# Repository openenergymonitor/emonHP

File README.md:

# emonHP - Heat Pump Monitoring

**As of Aug 2026 emonHP2 hardware is not yet released**

## Introduction

_emonHP V2_ is a system for monitoring heat pump operation. It is designed to work with [OpenEnergyMonitor](https://openenergymonitor.org), but can be used as a standalone system.

The system provides the following interfaces:

- MBUS
- RS485
- DHW, pulse, and OneWire (DS218B20 temperature) inputs
- USB-C power 
- 40-pin Raspberry Pi header
- OLED I2C display
- RFM69CW RF transceiver 

The board uses a STM32C031K6U microcontroller

## Getting started

### Getting a board

- Purchase a heat pump monitoring system from the [OpenEnergyMonitor Shop](https://shop.openenergymonitor.com/)
- Build your own!
  - With [KiCad](https://www.kicad.org/) installed, run `./generate.py` in the `pcb` directory (tested on Linux and macOS only) to generate manufacturing files (KiCad PCB, Gerbers, BoM).

### emonHP2

> [!NOTE]
Setting up as an integrated emonHP system requires a Raspberry Pi 4 or 5. These expose extra UART ports on the 40-pin header which are not available on older versions.

Connect the Raspberry Pi to the 40 pin header.

> [!WARNING]
Power must only be applied to one of the emonHP's USB-C port *or* the Raspberry Pi's power port, never both.

### Connections 

- DHW Status: Signal 1 input - GPIO27 - Pin 13 
- Pulse: Signal 2 input - GPIO22 - Pin15 - soft-pull down enabled (NOT TESTED)
- OneWire (DS18B20 ) - Signal 3 input - GPIO0*

\* Set `dtoverlay=w1-gpio,gpiopin=0` in `/boot/firmware/config.txt` to support OneWire on GPIO0

 - Push button - GPIO17 - pin11: set `push_btn = Button(17, pull_up=True, bounce_time=0.1, hold_time=5)` in `emonPiLCD2.py` 

### Firmware & Rasi Setup 

See firmware repo: https://github.com/openenergymonitor/emonhp-rs

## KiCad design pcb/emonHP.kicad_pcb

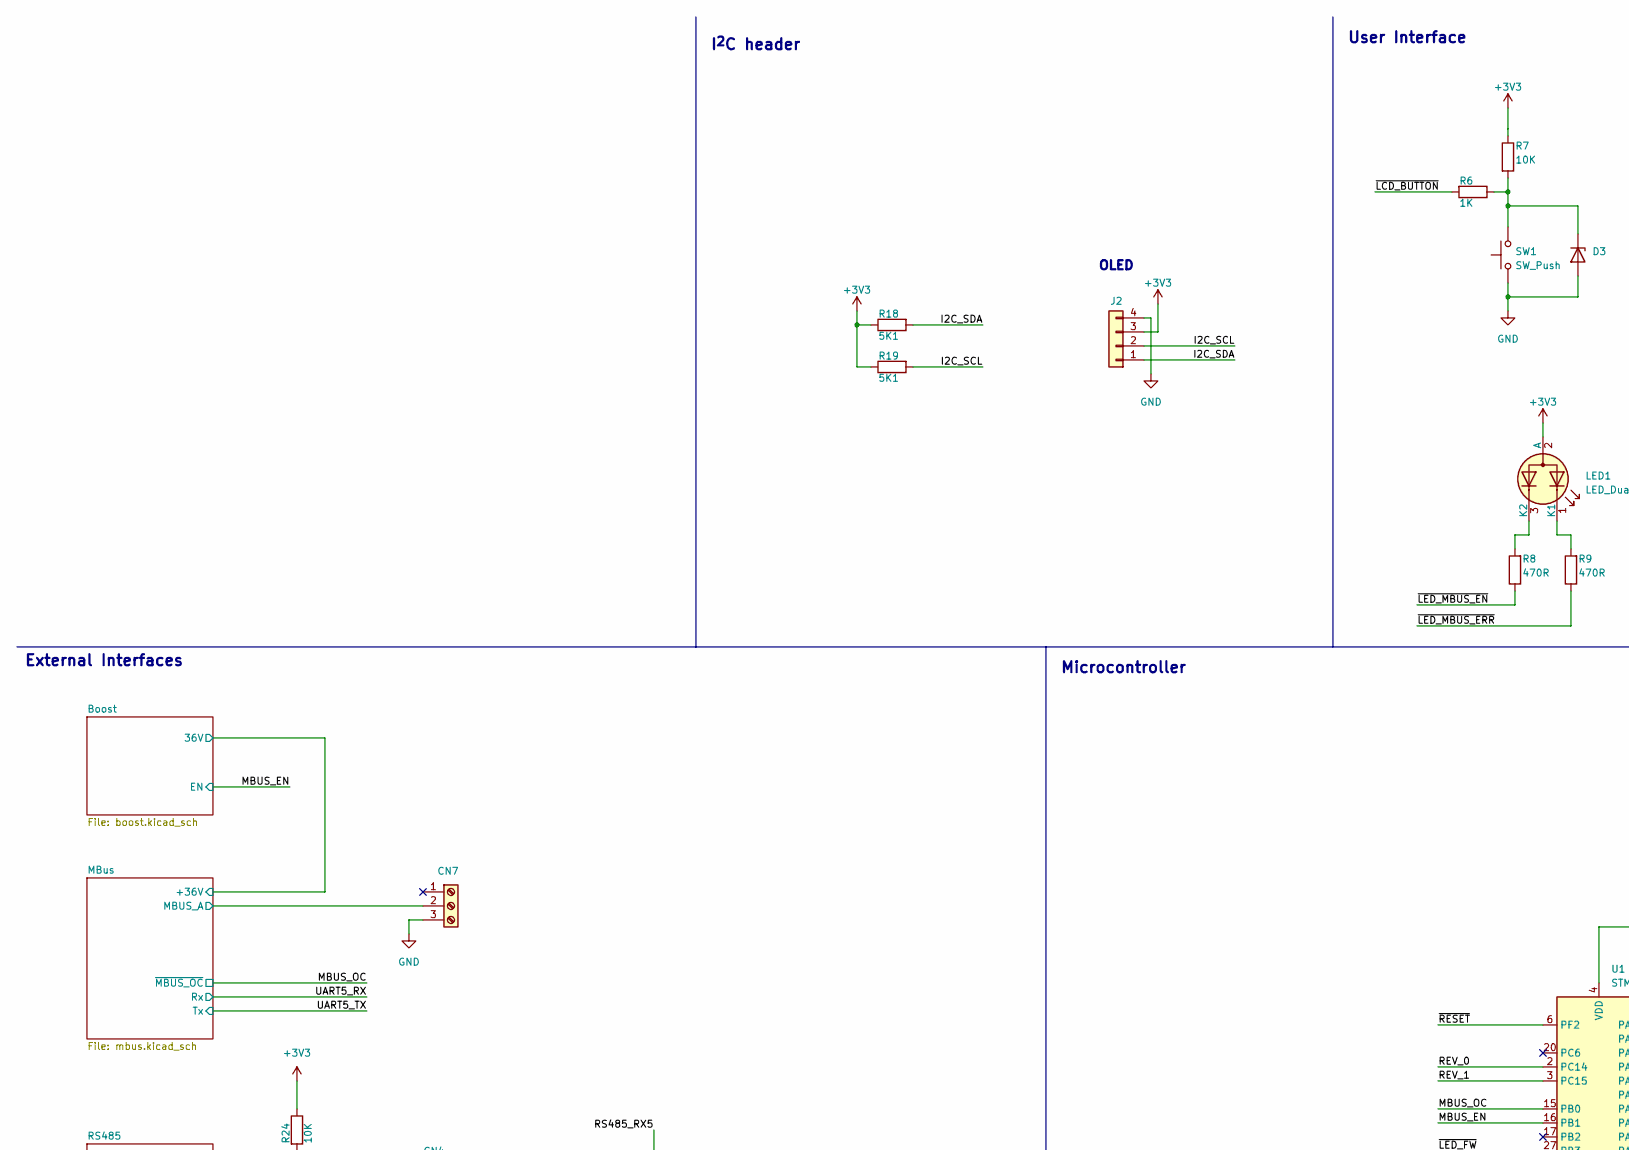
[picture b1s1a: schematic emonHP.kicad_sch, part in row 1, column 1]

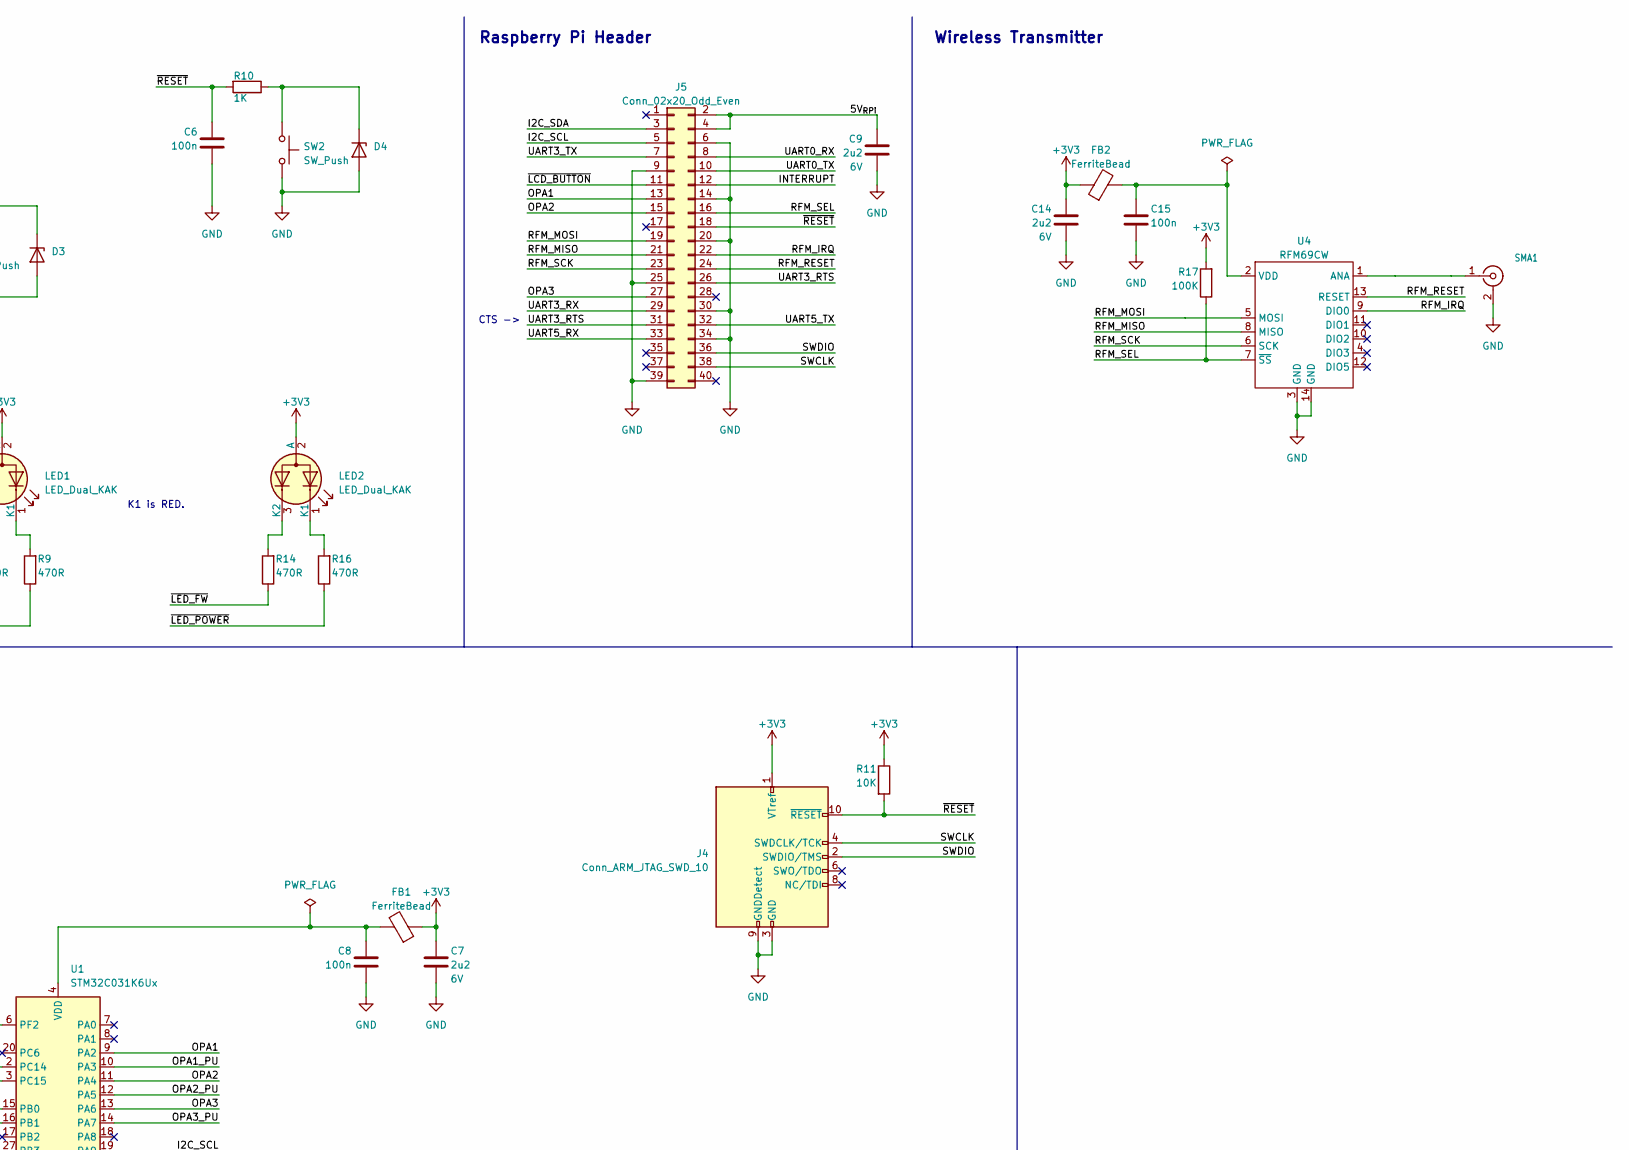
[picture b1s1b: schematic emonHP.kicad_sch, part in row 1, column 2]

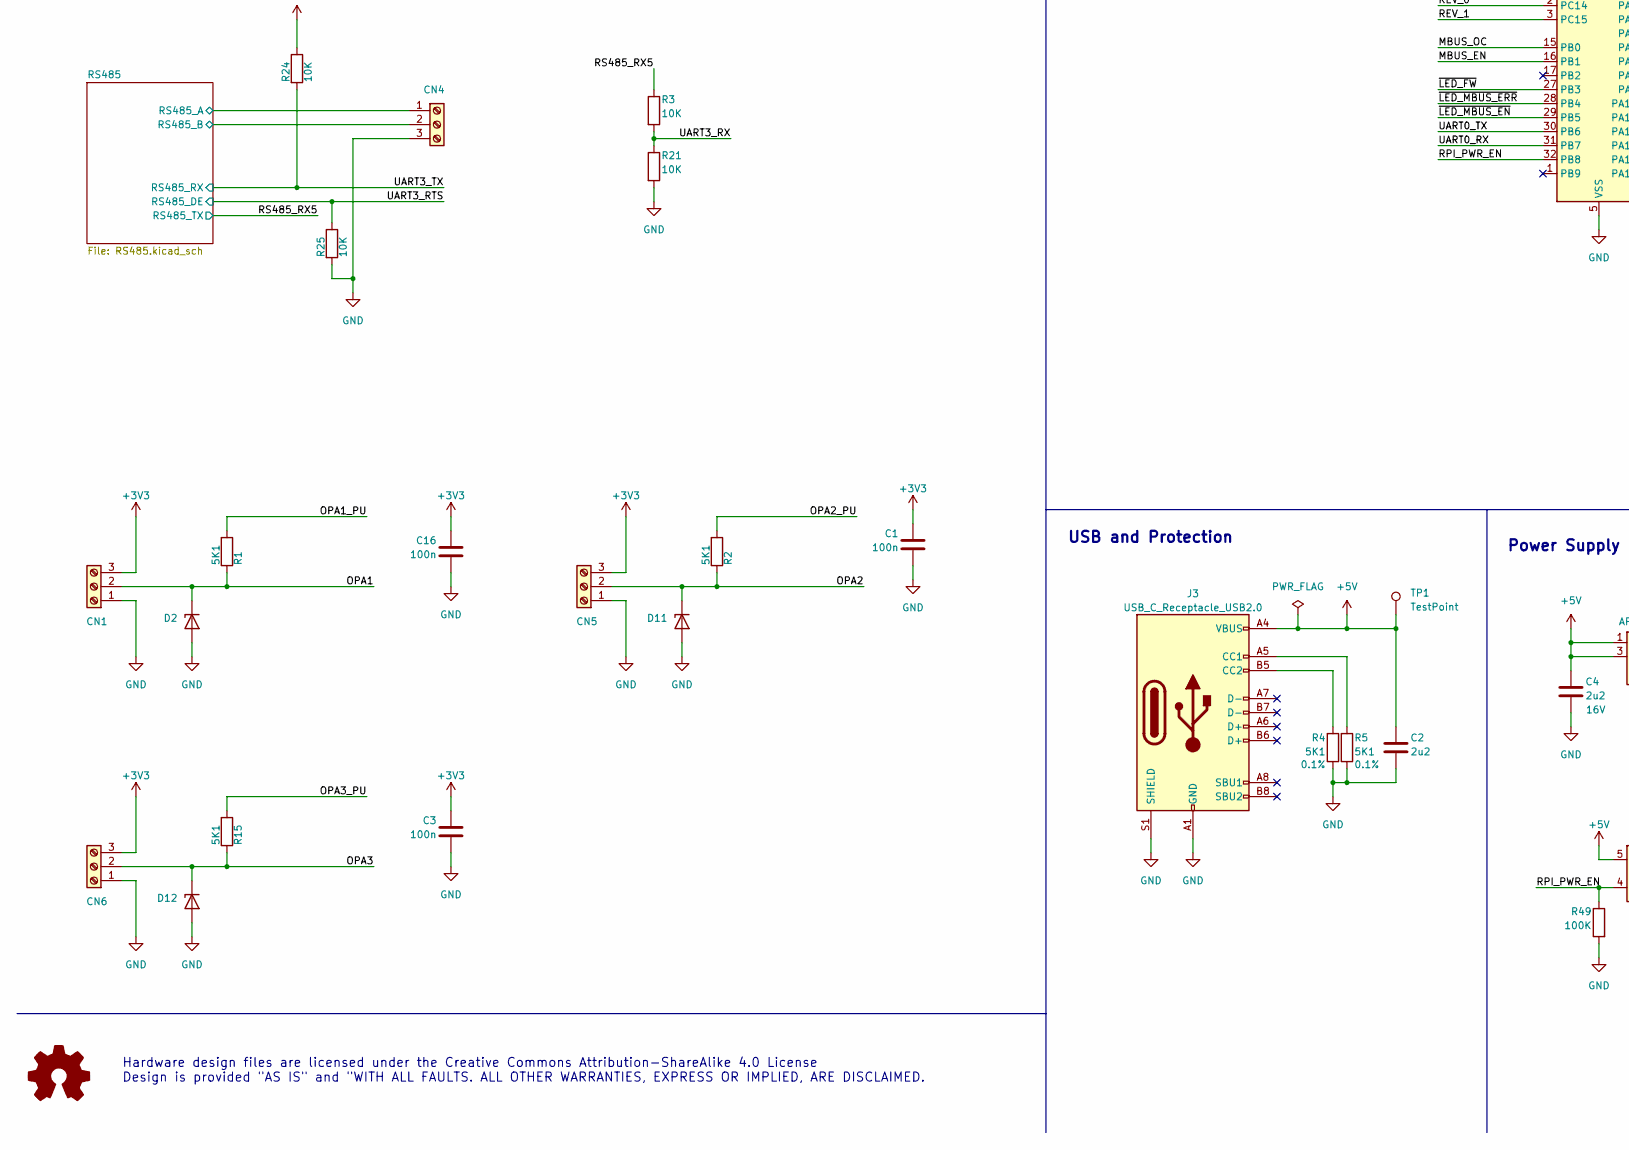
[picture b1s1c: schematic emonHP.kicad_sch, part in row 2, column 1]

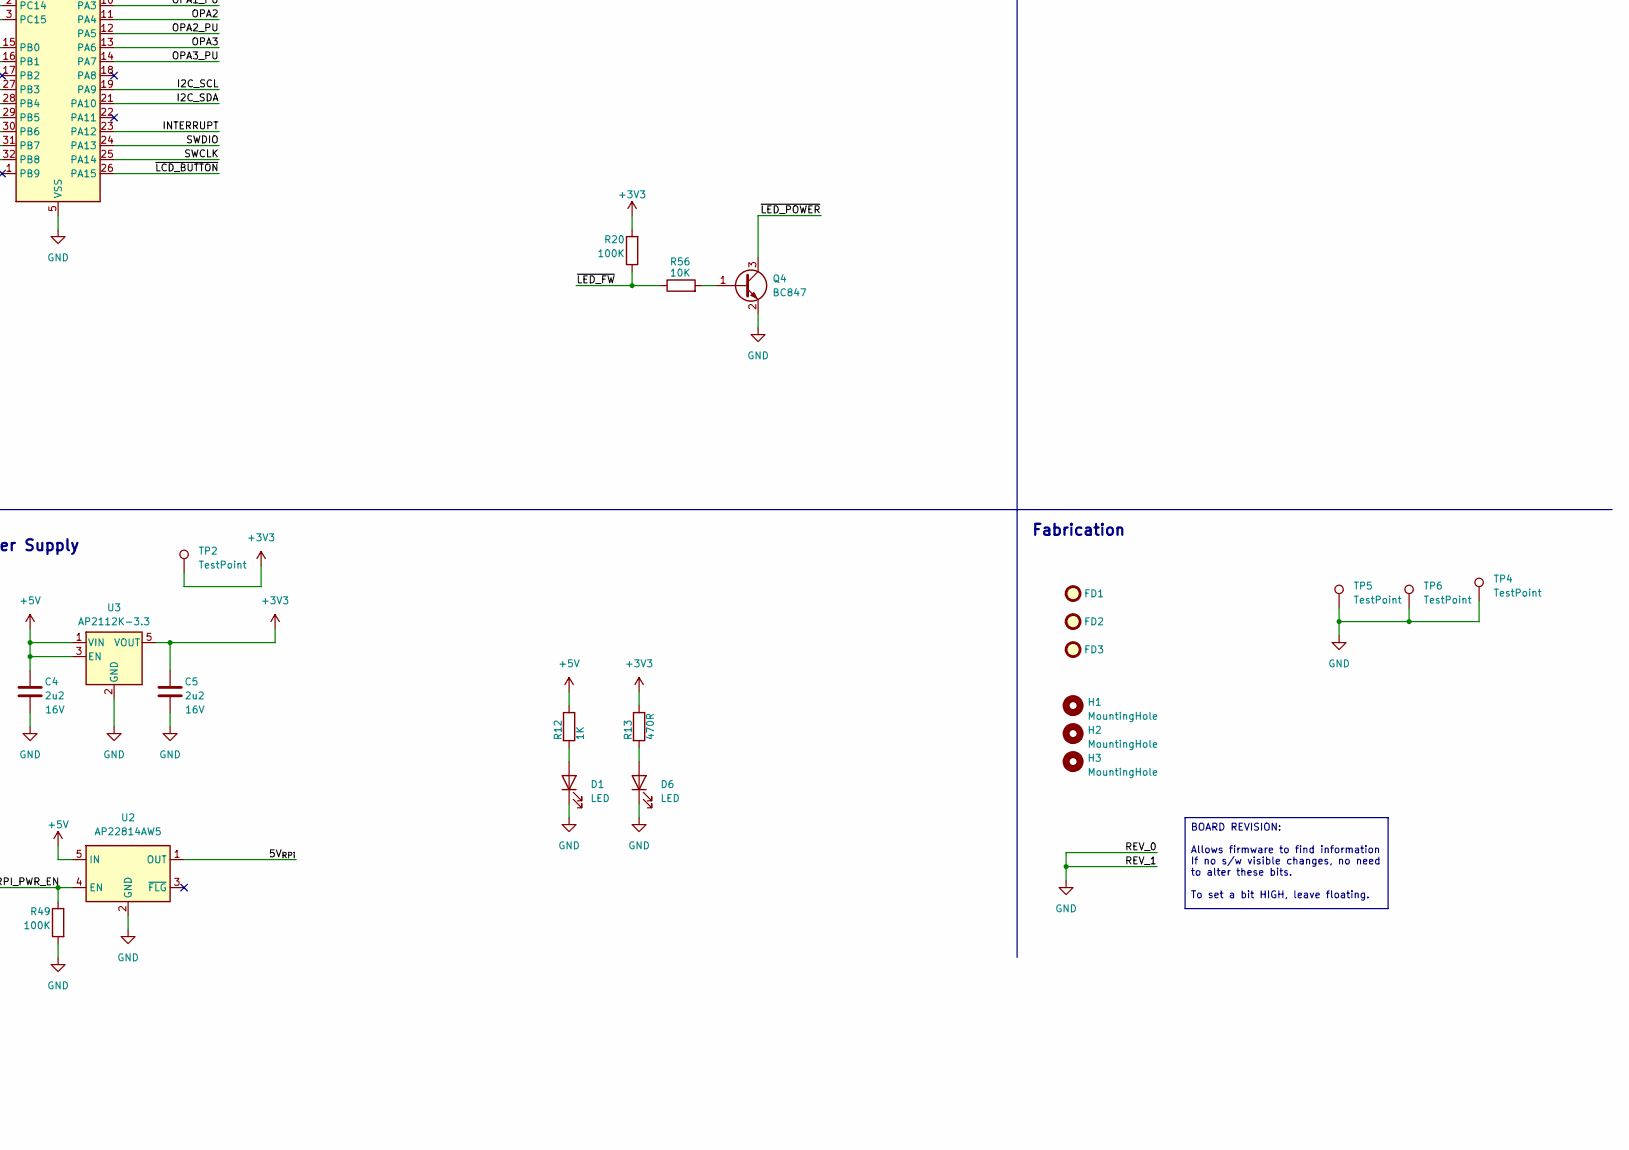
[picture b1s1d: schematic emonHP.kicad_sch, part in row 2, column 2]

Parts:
C1, C3, C6, C8, C15, C16: 100n; C_0402_1005Metric; LCSC C1525
C2: 2u2; C_0402_1005Metric; LCSC C12530
C4, C5: 2u2; C_0603_1608Metric; Voltage 16V; LCSC C23630
C7, C9, C14: 2u2; C_0402_1005Metric; Voltage 6V; LCSC C12530
CN1, CN4, CN5, CN6, CN7: CONN_03SCREW; TerminalBlock_Phoenix_PT-1,5-3-3.5-H_1x03_P3.50mm_Horizontal; MPN 5441359; Mouser 651-5441359
D1, D6: LED; LED_0603_1608Metric; LCSC C2286
D2, D3, D4, D11, D12: ESD5Z3.3T5G; D_SOD-523; LCSC C22440024
FB1, FB2: FerriteBead; R_0402_1005Metric; LCSC C237347
FD1, FD2, FD3: FIDUCIAL1X2; Fiducial_0.75mm_Mask1.5mm
H1, H2: MountingHole; MountingHole_2.7mm_M2.5
H3: MountingHole; MountingHole_2.1mm
J2: CONN_04PTH; PinSocket_1x04_P2.54mm_Vertical
J3: USB_C_Receptacle_USB2.0; CSP-USC16-TR; LCSC C2765186
J4: Conn_ARM_JTAG_SWD_10; PinHeader_2x05_P1.27mm_Vertical_SMD; LCSC C150517
J5: Conn_02x20_Odd_Even; REF-182665; LCSC C9900171940
LED1, LED2: LED_Dual_KAK; LTST-S326; MPN LTST-S326KGJRKT; Mouser 859-LTST-S326KGJRKT
Q4: BC847; SOT-23; LCSC C2138
R1, R2, R15, R18, R19: 5K1; R_0402_1005Metric; LCSC C25905
R3, R7, R11, R21, R24, R25, R56: 10K; R_0402_1005Metric; LCSC C25744
R4, R5: 5K1; R_0402_1005Metric; Tolerance 0.1%; MPN ERA-3AED512V; Mouser 667-ERA-3AED512V
R6, R10, R12: 1K; R_0402_1005Metric; LCSC C11702
R8, R9, R13, R14, R16: 470R; R_0402_1005Metric; LCSC C25117
R17, R20, R49: 100K; R_0402_1005Metric; LCSC C25741
SMA1: SMACONNECTOR; SMA_Amphenol_132203-12_Horizontal
SW1: SW_Push; SW_PUSH_6mm
SW2: SW_Push; SW_Tactile_SPST_NO_Straight_CK_PTS636Sx25SMTRLFS; LCSC C2689642
TP1, TP2, TP4, TP5, TP6: TestPoint; TestPoint_Pad_D1.0mm
U1: STM32C031K6Ux; QFN-32-1EP_5x5mm_P0.5mm_EP3.45x3.45mm; LCSC C5456204
U2: AP22814AW5; SOT-23-5; LCSC C2680321
U3: AP2112K-3.3; SOT-23-5; LCSC C51118
U4: RFM69CW

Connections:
+3V3: C1.1, C3.1, C5.2, C7.1, C14.1, C16.1, CN1.3, CN5.3, CN6.3, FB1.1, FB2.1, J2.3, J4.1 (VTref), LED1.2 (A), LED2.2 (A), R7.1, R11.1, R13.1, R17.2, R18.1, R19.1, R20.2, R24.1, TP2.1, U3.5 (VOUT); also elsewhere on the board
+5V: C2.2, C4.2, J3.A4 (VBUS), J3.A9 (VBUS), J3.B4 (VBUS), J3.B9 (VBUS), R12.1, TP1.1, U2.5 (IN), U3.1 (VIN), U3.3 (EN); also elsewhere on the board
/5V_{RPi}: C9.1, J5.2, J5.4, U2.1 (OUT)
/I2C_SCL: J2.2, J5.5, R19.2, U1.19 (PA9)
/I2C_SDA: J2.1, J5.3, R18.2, U1.21 (PA10)
/INTERRUPT: J5.12, U1.23 (PA12)
/MBUS_EN: U1.16 (PB1); also elsewhere on the board
/MBUS_OC: U1.15 (PB0); also elsewhere on the board
/MBus/MBUS_A: CN7.2; also elsewhere on the board
/OPA1: CN1.2, D2.1 (K), J5.13, R1.1, U1.9 (PA2)
/OPA1_PU: R1.2, U1.10 (PA3)
/OPA2: CN5.2, D11.1 (K), J5.15, R2.1, U1.11 (PA4)
/OPA2_PU: R2.2, U1.12 (PA5)
/OPA3: CN6.2, D12.1 (K), J5.27, R15.1, U1.13 (PA6)
/OPA3_PU: R15.2, U1.14 (PA7)
/RFM_IRQ: J5.22, U4.9 (DIO0)
/RFM_MISO: J5.21, U4.8 (MISO)
/RFM_MOSI: J5.19, U4.5 (MOSI)
/RFM_RESET: J5.24, U4.13 (RESET)
/RFM_SCK: J5.23, U4.6 (SCK)
/RFM_SEL: J5.16, R17.1, U4.7 (~SS)
/RPI_PWR_EN: R49.1, U1.32 (PB8), U2.4 (EN)
/RS485/RS485_A: CN4.1; also elsewhere on the board
/RS485/RS485_B: CN4.2; also elsewhere on the board
/RS485_RX5: R3.1; also elsewhere on the board
/SWCLK: J4.4 (SWDCLK/TCK), J5.38, U1.25 (PA14)
/SWDIO: J4.2 (SWDIO/TMS), J5.36, U1.24 (PA13)
/UART0_RX: J5.8, U1.31 (PB7)
/UART0_TX: J5.10, U1.30 (PB6)
/UART3_RTS: J5.26, J5.31, R25.1; also elsewhere on the board
/UART3_RX: J5.29, R3.2, R21.1
/UART3_TX: J5.7, R24.2; also elsewhere on the board
/UART5_RX: J5.33; also elsewhere on the board
/UART5_TX: J5.32; also elsewhere on the board
/~LCD_BUTTON: J5.11, R6.2, U1.26 (PA15)
/~LED_FW: R14.1, R20.1, R56.1, U1.27 (PB3)
/~LED_MBUS_EN: R8.1, U1.29 (PB5)
/~LED_MBUS_ERR: R9.1, U1.28 (PB4)
/~LED_POWER: Q4.3 (C), R16.1
/~RESET: C6.1, J4.10 (~RESET), J5.18, R10.2, R11.2, U1.6 (PF2)
GND: C1.2, C2.1, C3.2, C4.1, C5.1, C6.2, C7.2, C8.2, C9.2, C14.2, C15.2, C16.2, CN1.1, CN4.3, CN5.1, CN6.1, CN7.3, D1.1 (K), D2.2 (A), D3.2 (A), D4.2 (A), D6.1 (K), D11.2 (A), D12.2 (A), J2.4, J3.A1 (GND), J3.A12 (GND), J3.B1 (GND), J3.B12 (GND), J3.S1 (SHIELD), J4.3 (GND), J4.5 (GND), J4.9 (GNDDetect), J5.6, J5.9, J5.14, J5.20, J5.25, J5.30, J5.34, J5.39, Q4.2 (E), R4.1, R5.1, R21.2, R25.2, R49.2, SMA1.2 (Ext), SW1.1, SW2.2, TP4.1, TP5.1, TP6.1, U1.2 (PC14), U1.3 (PC15), U1.5 (VSS), U1.33 (VSS), U2.2 (GND), U3.2 (GND), U4.3 (GND), U4.14 (GND); also elsewhere on the board
unnamed: D1.2 (A), R12.2
unnamed: D3.1 (K), R6.1, R7.2, SW1.2
unnamed: D4.1 (K), R10.1, SW2.1
unnamed: D6.2 (A), R13.2
unnamed: J3.A5 (CC1), R5.2
unnamed: J3.B5 (CC2), R4.2
unnamed: LED1.1 (K1), R9.2
unnamed: LED1.3 (K2), R8.2
unnamed: LED2.1 (K1), R16.2
unnamed: LED2.3 (K2), R14.2
unnamed: Q4.1 (B), R56.2
unnamed: SMA1.1 (In), U4.1 (ANA)
unnamed: C8.1, FB1.2, U1.4 (VDD)
unnamed: C15.1, FB2.2, U4.2 (VDD)

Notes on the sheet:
Raspberry Pi Header
Power Supply
CTS ->
Hardware design files are licensed under the Creative Commons Attribution-ShareAlike 4.0 License Design is provided "AS IS" and "WITH ALL FAULTS. ALL OTHER WARRANTIES, EXPRESS OR IMPLIED, ARE DISCLAIMED.
Microcontroller
User Interface
K1 is RED.
USB and Protection
Fabrication
OLED
External Interfaces
I^{2}C header
Wireless Transmitter
BOARD REVISION: Allows firmware to find information If no s/w visible changes, no need to alter these bits. To set a bit HIGH, leave floating.

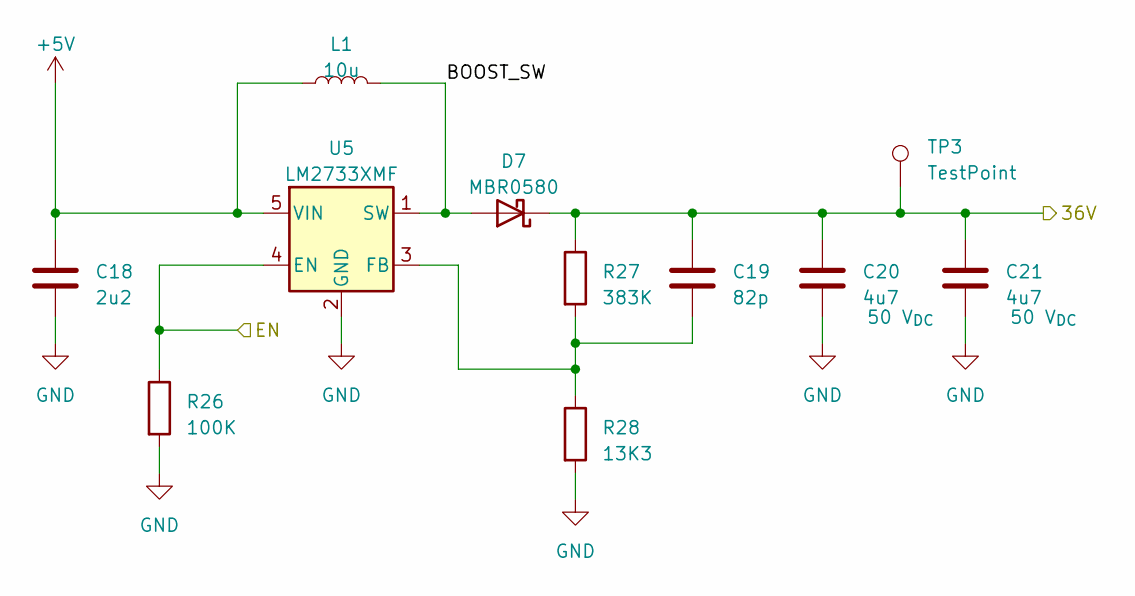
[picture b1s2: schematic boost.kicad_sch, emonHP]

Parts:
C18: 2u2; C_0603_1608Metric; LCSC C23630
C19: 82p; C_0603_1608Metric; LCSC C1683
C20, C21: 4u7; C_0805_2012Metric; Voltage 50 V_{DC}; MPN GRM21BZ71H475ME15L; LCSC C98192
D7: MBR0580; D_SOD-123; LCSC C177047
L1: 10u; L_Abracon_ASPI-3012S; MPN ASPI-3012S-100M-T; Mouser 815-ASPI-3012S-100MT
R26: 100K; R_0402_1005Metric; LCSC C25741
R27: 383K; R_0402_1005Metric; LCSC C25557
R28: 13K3; R_0402_1005Metric; LCSC C122547
TP3: TestPoint; TestPoint_Pad_D1.0mm
U5: LM2733XMF; SOT-23-5; MPN LM2733XMFX/NOPB; Mouser 926-LM2733XMFX/NOPB

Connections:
+5V: C18.1, L1.2, U5.5 (VIN); also elsewhere on the board
/Boost/BOOST_SW: D7.2 (A), L1.1, U5.1 (SW)
/MBUS_EN: R26.1, U5.4 (EN); also elsewhere on the board
/MBus/36V: C19.1, C20.1, C21.1, D7.1 (K), R27.1, TP3.1; also elsewhere on the board
GND: C18.2, C20.2, C21.2, R26.2, R28.2, U5.2 (GND); also elsewhere on the board
unnamed: C19.2, R27.2, R28.1, U5.3 (FB)

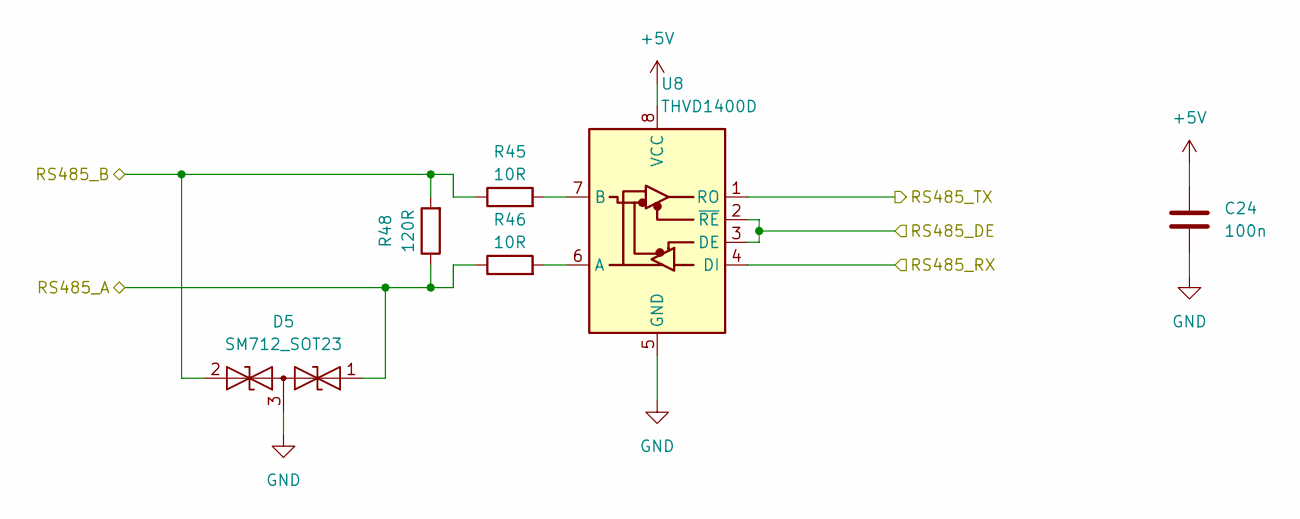
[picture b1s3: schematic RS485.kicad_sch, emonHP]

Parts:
C24: 100n; C_0402_1005Metric; LCSC C1525
D5: SM712_SOT23; SOT-23; LCSC C172881
R45, R46: 10R; R_0603_1608Metric; LCSC C22859
R48: 120R; R_1206_3216Metric; LCSC C17909
U8: THVD1400D; SOIC-8_3.9x4.9mm_P1.27mm; LCSC C3235232

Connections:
+5V: C24.1, U8.8 (VCC); also elsewhere on the board
/RS485/RS485_A: D5.1 (A1), R46.1, R48.1; also elsewhere on the board
/RS485/RS485_B: D5.2 (A2), R45.1, R48.2; also elsewhere on the board
/RS485_RX5: U8.1 (RO); also elsewhere on the board
/UART3_RTS: U8.2 (~RE), U8.3 (DE); also elsewhere on the board
/UART3_TX: U8.4 (DI); also elsewhere on the board
GND: C24.2, D5.3 (common), U8.5 (GND); also elsewhere on the board
unnamed: R46.2, U8.6 (A)
unnamed: R45.2, U8.7 (B)

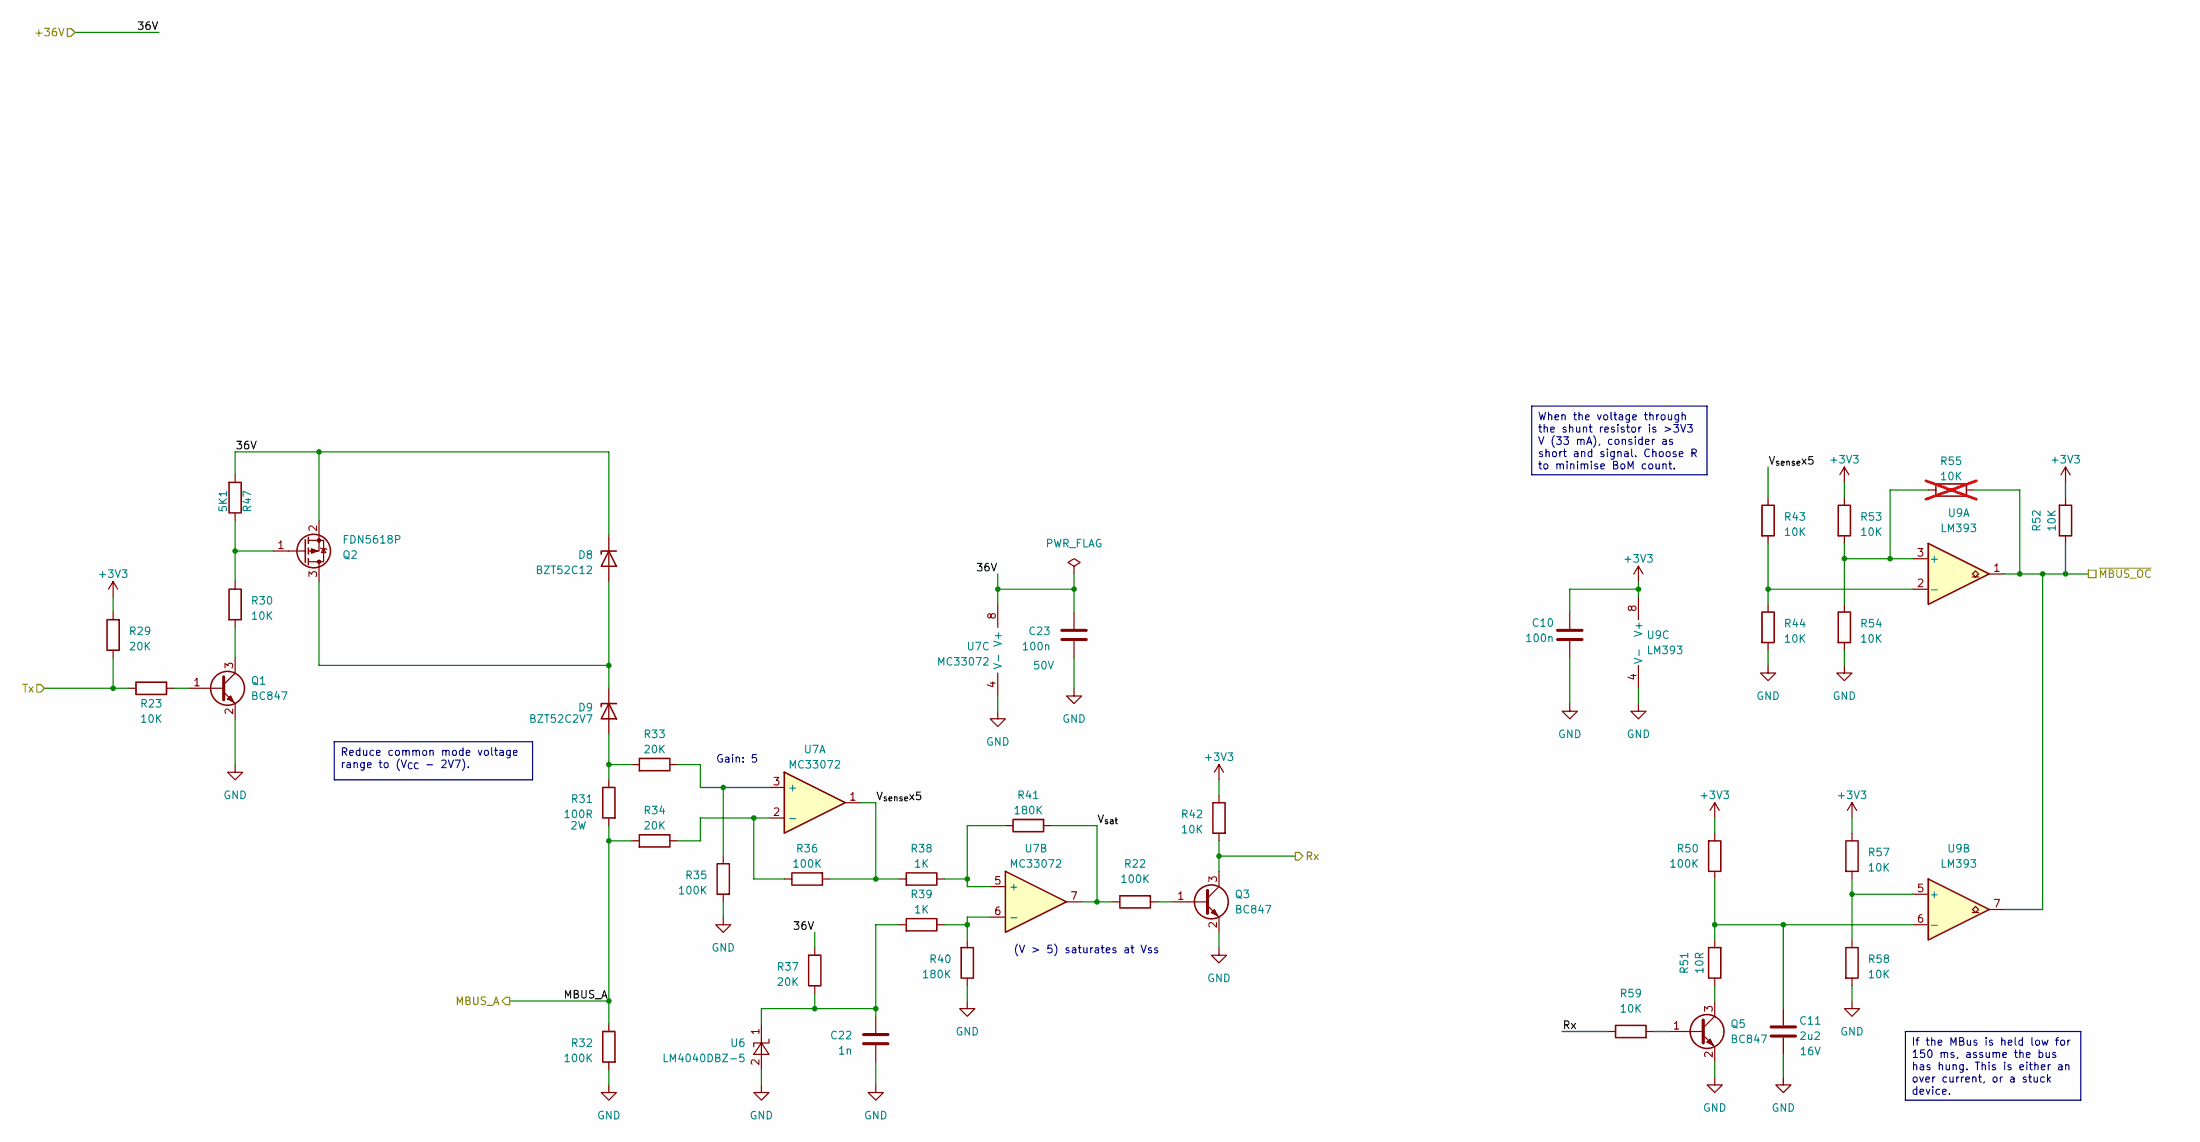
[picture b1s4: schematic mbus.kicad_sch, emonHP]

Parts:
C10: 100n; C_0402_1005Metric; LCSC C1525
C11: 2u2; C_0603_1608Metric; Voltage 16V; LCSC C23630
C22: 1n; C_0402_1005Metric; LCSC C1523
C23: 100n; C_0402_1005Metric; Voltage 50V; LCSC C307331
D8: BZT52C12; D_SOD-123F; LCSC C124196
D9: BZT52C2V7; D_SOD-123F; LCSC C5244698
Q1, Q3, Q5: BC847; SOT-23; LCSC C2138
Q2: FDN5618P; SOT-23; LCSC C400792
R22, R32, R35, R36, R50: 100K; R_0402_1005Metric; LCSC C25741
R23, R30, R42, R43, R44, R52, R53, R54, R57, R58, R59: 10K; R_0402_1005Metric; LCSC C25744
R29, R33, R34, R37: 20K; R_0402_1005Metric; LCSC C25765
R31: 100R; R_2512_6332Metric; MPN CRM2512-JW-101ELF; Mouser 652-CRM2512-JW101ELF
R38, R39: 1K; R_0402_1005Metric; LCSC C11702
R40, R41: 180K; R_0402_1005Metric; LCSC C25760
R47: 5K1; R_0402_1005Metric; LCSC C25905
R51: 10R; R_0603_1608Metric; LCSC C22859
R55: 10K; R_0402_1005Metric; LCSC C25744; not fitted
U6: LM4040DBZ-5; SOT-23; MPN LM4040DYM3-5.0-TR; Mouser 998-LM4040DYM3-5.0TR
U7: MC33072; SOIC-8_3.9x4.9mm_P1.27mm; MPN MC33072DR2G; Mouser 863-MC33072DR2G
U9: LM393; SOIC-8_3.9x4.9mm_P1.27mm; LCSC C7955

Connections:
+3V3: C10.1, R29.2, R42.1, R50.2, R52.2, R53.1, R57.1, U9.8 (V+); also elsewhere on the board
/MBUS_OC: R52.1, R55.2, U9.1, U9.7; also elsewhere on the board
/MBus/36V: C23.1, D8.1 (K), Q2.2 (S), R37.2, R47.2, U7.8 (V+); also elsewhere on the board
/MBus/MBUS_A: R31.2, R32.1, R34.2; also elsewhere on the board
/MBus/V_{sat}: R22.1, R41.2, U7.7
/MBus/V_{sense}x5: R36.2, R38.2, R43.1, U7.1
/UART5_RX: Q3.3 (C), R42.2, R59.1; also elsewhere on the board
/UART5_TX: R23.1, R29.1; also elsewhere on the board
GND: C10.2, C11.1, C22.2, C23.2, Q1.2 (E), Q3.2 (E), Q5.2 (E), R32.2, R35.2, R40.1, R44.2, R54.2, R58.2, U6.2 (A), U7.4 (V-), U9.4 (V-); also elsewhere on the board
unnamed: D8.2 (A), D9.1 (K), Q2.3 (D)
unnamed: D9.2 (A), R31.1, R33.2
unnamed: Q1.1 (B), R23.2
unnamed: Q1.3 (C), R30.2
unnamed: Q2.1 (G), R30.1, R47.1
unnamed: Q3.1 (B), R22.2
unnamed: Q5.1 (B), R59.2
unnamed: Q5.3 (C), R51.1
unnamed: C22.1, R37.1, R39.2, U6.1 (K)
unnamed: R33.1, R35.1, U7.3 (+)
unnamed: R34.1, R36.1, U7.2 (-)
unnamed: R38.1, R41.1, U7.5 (+)
unnamed: R39.1, R40.2, U7.6 (-)
unnamed: R53.2, R54.1, R55.1, U9.3 (+)
unnamed: R43.2, R44.1, U9.2 (-)
unnamed: R57.2, R58.1, U9.5 (+)
unnamed: C11.2, R50.1, R51.2, U9.6 (-)

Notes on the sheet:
Gain: 5
(V > 5) saturates at Vss
When the voltage through the shunt resistor is >3V3 V (33 mA), consider as short and signal. Choose R to minimise BoM count.
If the MBus is held low for 150 ms, assume the bus has hung. This is either an over current, or a stuck device.
Reduce common mode voltage range to (V_{CC} - 2V7).

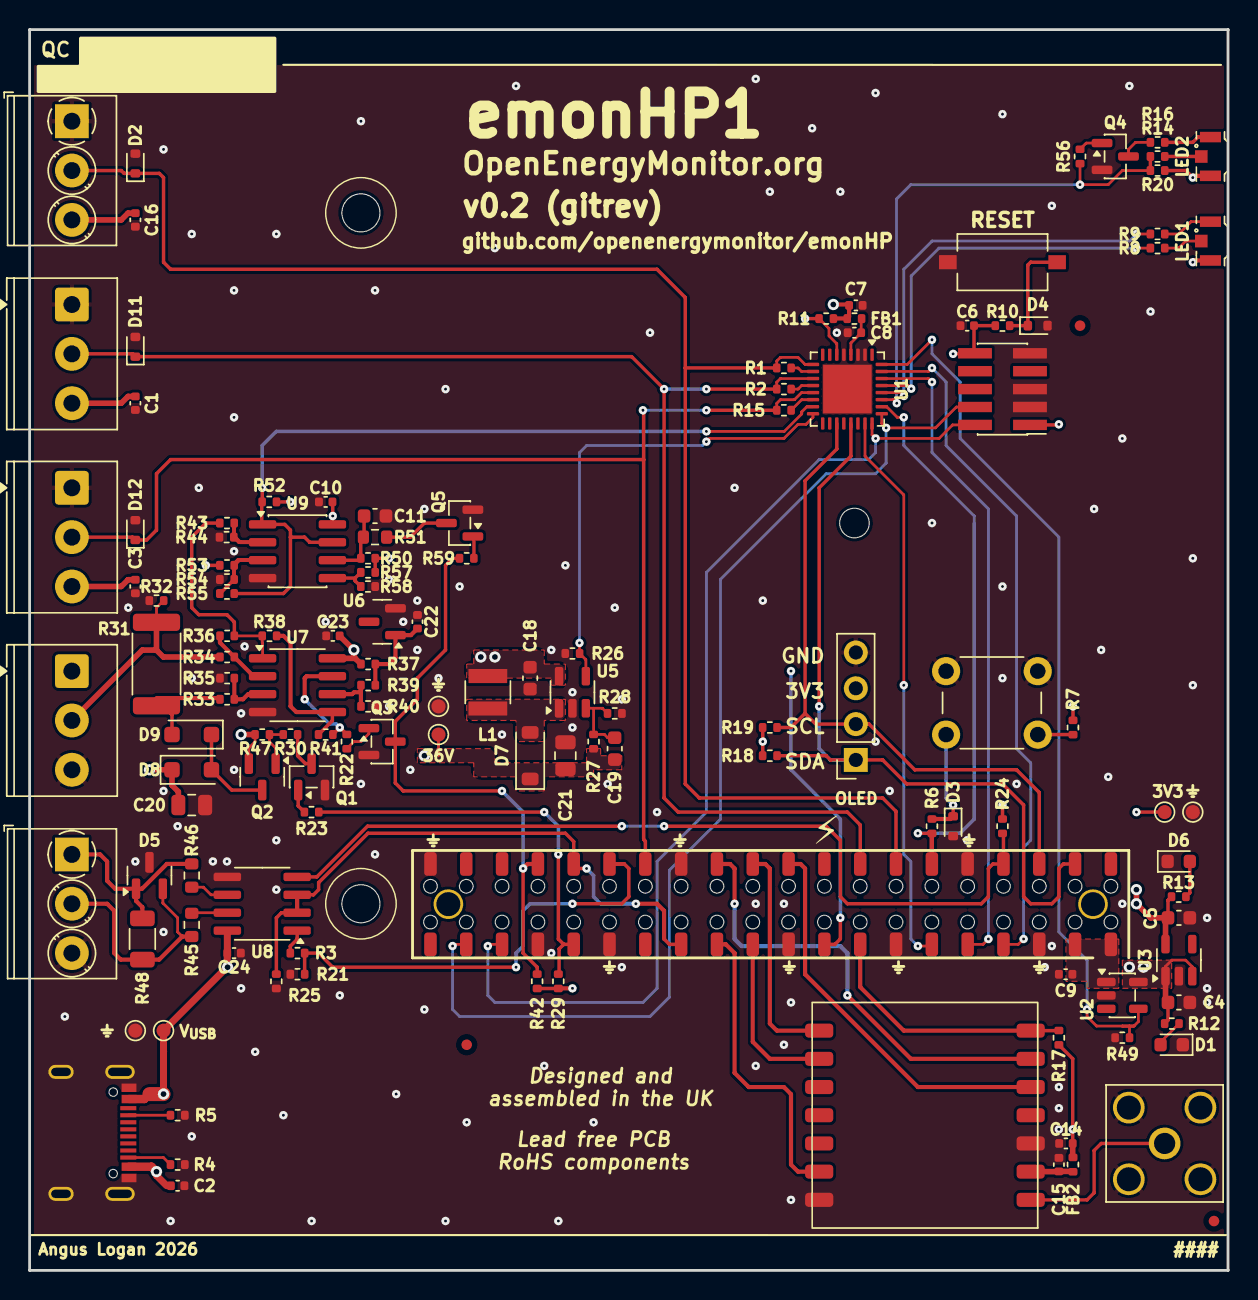
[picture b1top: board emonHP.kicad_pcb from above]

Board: 4 copper layers, 85.0 x 88.0 mm, 134 parts (0 on the bottom side), 79 nets.

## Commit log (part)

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2025-07-29 Manufactured board
2026-04-13 emonHP with Pi attachment
